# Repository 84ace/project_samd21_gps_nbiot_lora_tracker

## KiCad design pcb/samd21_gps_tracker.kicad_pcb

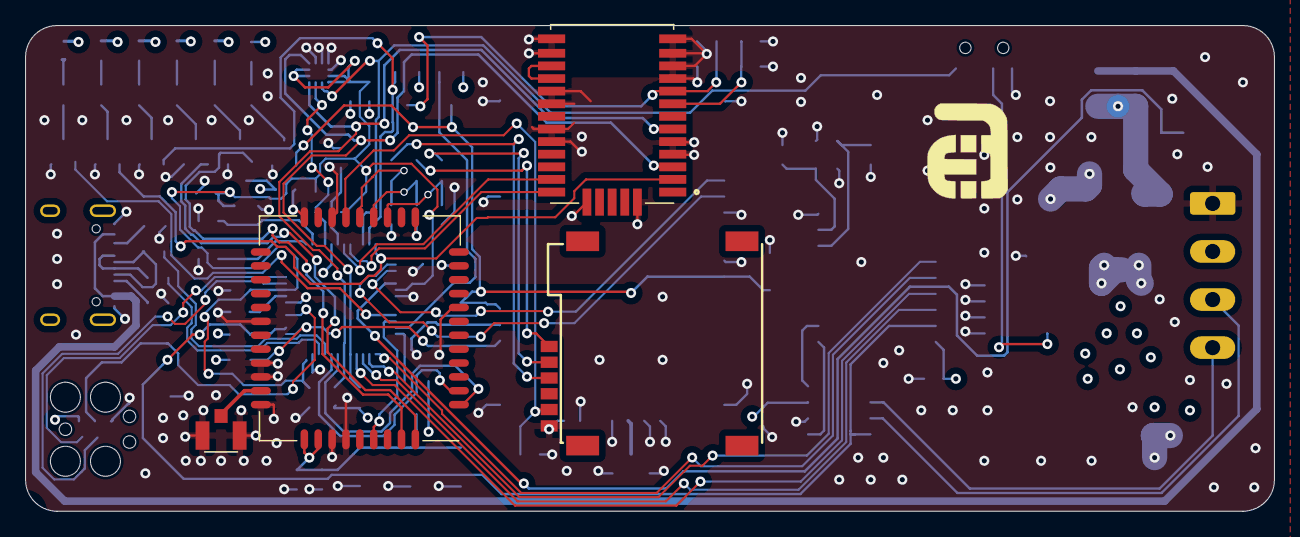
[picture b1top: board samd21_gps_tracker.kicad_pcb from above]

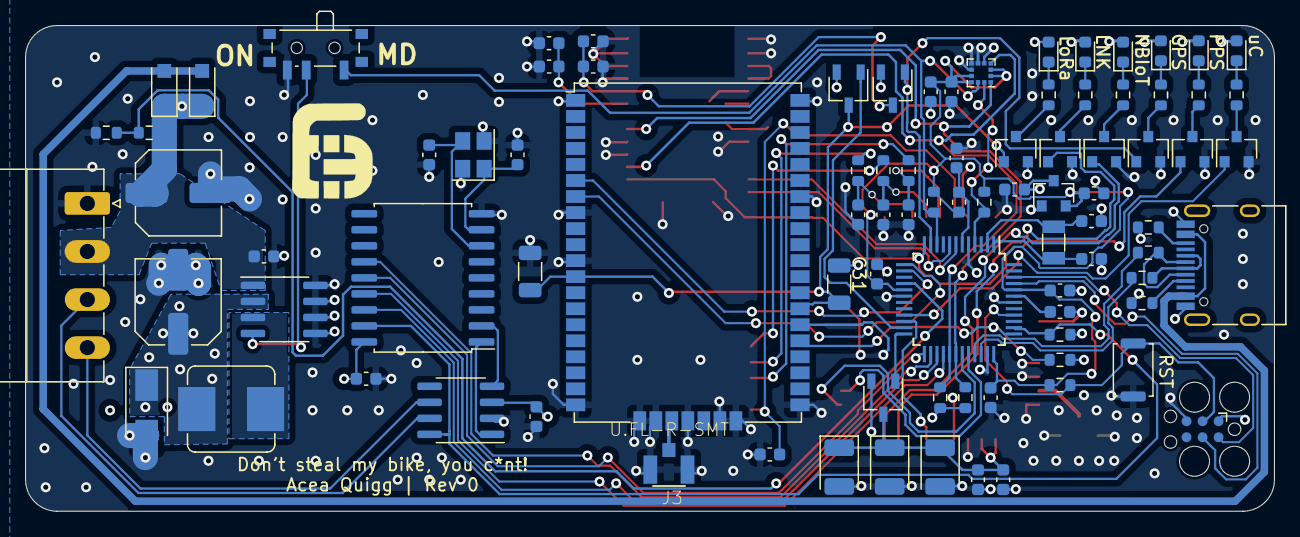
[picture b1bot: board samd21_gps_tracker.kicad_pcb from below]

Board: 4 copper layers, 99.0 x 38.5 mm, 95 parts (90 on the bottom side), 76 nets.

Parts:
C1, C2, C11, C12: 12.5pF; C_0603_1608Metric
C3, C4, C8, C9, C10, C14, C15, C16, C21, C25, C26, C31: 100nF; C_0603_1608Metric
C5: 10nF; C_0603_1608Metric
C6, C7: 220uF; C_Elec_6.3x7.7
C13, C17: 47uF; C_1206_3216Metric
C18, C19, C20, C32, C33: 10uF; C_0603_1608Metric
C22, C23, C24: 22pF; C_0603_1608Metric
C27: 1uF; C_0603_1608Metric
C28, C29, C30: 100uF; CP_EIA-3528-21_Kemet-B
D1: Red_uC_State; LED_0603_1608Metric
D2: Red_GPS_PPS; LED_0603_1608Metric
D3: D_Small; D_SMA
D4: Red_GPS_PWR; LED_0603_1608Metric
D5: Red_Modem_Status; LED_0603_1608Metric
D6: Red_Modem_Link; LED_0603_1608Metric
D7, D8: B5817WL; D_SOD-123F
D9: Red_LoRa_PWR; LED_0603_1608Metric
FB1: 30 Ohm; L_0603_1608Metric
J1: JTAG_SWD_6; Tag-Connect_TC2030-IDC-FP_2x03_P1.27mm_Vertical
J2: 01x04; PhoenixContact_MC_1,5_4-G-3.81_1x04_P3.81mm_Horizontal
J3, J6: U.FL-R-SMT
J4: SIM_Card; SIM-002-A6
J5: USB_C_Receptacle_USB2.0; USB_C_Receptacle_HRO_TYPE-C-31-M-12
J7: C7244; aces_electronics_small
L1: L_Small; L_Bourns_SRP7028A_7.3x6.6mm
Q1, Q2, Q3, Q4, Q5, Q9: 2N7002; SOT-23
Q6, Q7, Q8: Q_PMOS_GSD; TSOT-23
R1, R2, R4, R5, R8, R9, R10, R20: 3k; R_0603_1608Metric
R3: 10k; R_0603_1608Metric
R6, R7, R11, R12, R21: 100k; R_0603_1608Metric
R13, R14, R15, R18, R19: 27R; R_0603_1608Metric
R16, R17: 5.1k; R_0603_1608Metric
R22: 22k; R_0603_1608Metric
SW1: SW_Push; SW_Push_SPST_NO_Alps_SKRK
SW2: SW_Push_SPDT; SW_SPDT_PCM12
U1: XL1509_SOP8; SOIC-8_3.9x4.9mm_P1.27mm
U2: ATSAMD21G18A-A; TQFP-48_7x7mm_P0.5mm
U3: MCP2515-xSO; SOIC-18W_7.5x11.6mm_P1.27mm
U4: L96-M33; XCVR_L96-M33
U5: RN2903; RN2483
U6: MCP2551-I-SN; SOIC-8_3.9x4.9mm_P1.27mm
U7: LIS2DE12; LGA-12_2x2mm_P0.5mm
U8: SIM7020E; SIMCom_SIM800C
U9: ME6208; SOT-23
Y1: 32.768k; Crystal_SMD_3215-2Pin_3.2x1.5mm
Y2: 16mHz; Crystal_SMD_3225-4Pin_3.2x2.5mm

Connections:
3V3: C3.1, C8.1, C20.1, C21.1, C31.1, C33.2, FB1.1, R3.1, R11.1, R12.1, U2.17, U2.36, U2.44, U7.2, U7.3, U7.9, U7.10, U9.2
+3V3: C7.1, C10.1, C14.1, C16.1, C18.1, D1.2, D2.2, D3.1, D4.2, D5.2, D6.2, D9.2, J1.1, L1.2, Q6.2, Q7.2, Q8.2, R1.1, R2.1, R6.1, R7.1, U1.2, U3.18, U4.8, U6.3
+5V: D7.2, D8.2, J5.A4, J5.A9, J5.B4, J5.B9
BATT_ADC: R21.2, R22.1, U2.16
CAN_RST: R7.2, U2.38, U3.17, U6.8
CH: J2.3, U6.7
CL: J2.4, U6.6
D10-SS: U2.27, U3.16
D11-MOSI: U2.25, U3.14
D12-MISO: U2.28, U3.15
D13-SCK: U2.26, U3.13
GND: C1.1, C2.2, C3.2, C4.2, C5.2, C6.2, C7.2, C8.2, C9.2, C10.2, C11.2, C12.2, C13.2, C14.2, C15.2, C16.2, C17.2, C18.2, C19.2, C20.2, C21.2, C22.2, C23.2, C24.2, C25.2, C26.2, C27.2, C28.2, C29.2, C30.2, C31.2, C32.2, C33.1, D3.2, J1.5, J2.1, J3.1, J3.2, J4.5, J5.A1, J5.A12, J5.B1, J5.B12, J6.1, J6.2, Q1.2, Q2.2, Q3.2, Q4.2, Q5.2, Q9.2, R16.2, R17.2, R22.2, SW1.1, SW2.3, U1.5, U1.6, U1.7, U1.8, U2.5, U2.18, U2.35, U2.42, U3.9, U4.4, U4.5, U4.10, U4.11, U4.12, U4.13, U4.14, U4.15, U4.18, U4.19, U4.21, U4.22, U4.27, U4.31, U5.1, U5.8, U5.11, U5.20, U5.21, U5.22, U5.24, U5.26, U5.27, U5.28, U5.33, U5.41, U5.47, U6.2, U7.5, U7.6, U7.7, U7.8, U8.8, U8.13, U8.19, U8.21, U8.27, U8.30, U8.31, U8.33, U8.36, U8.37, U9.1, Y2.2, Y2.4
GPS_ON: Q3.1, Q7.1, U2.11
GPS_RX: U2.8, U4.26
GPS_TX: U2.7, U4.25
INT1: R11.2, U2.4, U7.12
INT2: R12.2, SW2.1, U2.10, U7.11
LoRa_ON: Q6.1, U2.23
LoRa_VCC: C13.1, C17.1, Q6.3, Q9.1, U5.12, U5.34
NETLIGHT: Q5.1, U8.41
unnamed: C1.2, U2.1, Y1.2
unnamed: C2.1, U2.2, Y1.1
unnamed: C4.1, U2.43
unnamed: C9.1, FB1.2, U2.6
unnamed: C11.1, U3.7, Y2.3
unnamed: C12.1, U3.8, Y2.1
unnamed: C15.1, C19.1, Q7.3, U4.9
unnamed: C22.1, R13.1, U8.15
unnamed: C23.1, R14.1, U8.16
unnamed: C24.1, R15.1, U8.17
unnamed: C26.1, C27.1, C28.1, C29.1, C30.1, Q8.3, U8.34, U8.35
unnamed: D1.1, R4.1
unnamed: D2.1, R5.1
unnamed: D4.1, R8.1
unnamed: D5.1, R9.1
unnamed: D6.1, R10.1
unnamed: D9.1, R20.1
unnamed: J3.3, U5.23
unnamed: J5.A5, R16.1
unnamed: J5.A6, J5.B6, R19.1
unnamed: J5.A7, J5.B7, R18.1
unnamed: J5.B5, R17.1
unnamed: J6.3, U8.32
unnamed: L1.1, U1.3
unnamed: Q1.3, R4.2
unnamed: Q2.3, R5.2
unnamed: Q3.3, R8.2
unnamed: Q4.3, R9.2
unnamed: Q5.3, R10.2
unnamed: Q9.3, R20.2
unnamed: U4.16, U4.17
PPS: Q2.1, U2.12, U4.2
RN_RST: R6.2, U2.37, U5.32
RN_RX: U2.13, U5.7
RN_TX: U2.14, U5.6
SCL: R2.2, U2.30, U4.6, U7.1
SDA: R1.2, U2.29, U4.3, U7.4
SIM_CLK: J4.3, R14.2
SIM_DATA: J4.7, R13.2
SIM_ON: Q8.1, U2.24
SIM_PWRKEY: U2.22, U8.39
SIM_RST: J4.2, R15.2
SIM_RXD: U2.32, U8.2
SIM_TXD: U2.31, U8.1
SIM_VDD: C25.1, J4.1, U8.18
SN_R: U3.2, U6.4
SN_T: U3.1, U6.1
STATUS: Q4.1, U8.42
STATUS_LED: Q1.1, U2.21
SWCLK: J1.4, U2.45
SWDIO: J1.2, U2.46
USBD+: R19.2, U2.34
USBD-: R18.2, U2.33
VIN: C5.1, C6.1, C32.1, D7.1, D8.1, J2.2, R21.1, U1.1, U9.3
~EN: SW2.2, U1.4
~Reset: J1.3, R3.2, SW1.2, U2.40

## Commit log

2021-07-19 REV 0 - off to JLCPCB
    This is the first commit which includes the BOM, schematic, PCB and Gerber files.
2021-08-18 REV 1 - WIP
    Fixed D3, it was the wrong way around
    Fixed Q6, Q7, Q8, D and S were the wrong way around
